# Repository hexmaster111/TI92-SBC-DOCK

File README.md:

**NOTE**
The Zero version is not currently being worked on and is an unusable state

# TI92 - CM4

TODO
--------
- [ ] Whats gonna happon is im gonna get a 4 inch hdmi display and desolder the hdmi connector and add it to a ribbion cable and then add a connector to the pcb for hdmi to interface with that
- [ ] Add a SD card slot
- [x] Figure out what display to use
- [ ] Add a headphone port
- [x] Add a USB Hub
	- [ ] Route USB in a good way :wink:
- [x] Get a charge solution sorted
- [x] Figure out how the keyboard will work and talk to the pi
- [ ] TEST
- [ ] Write code for the ATTINY85 (aka power control chip)
	- [ ] ~~Find a better way to switch power?~~
 - [ ] Use the micro USB that is used for charging to also act as USB OTG for flashing the CM4
 - [ ] Figure out a low voltage cut off for the batCell+ line
 - [ ] Calculate R4 on the charge chip
 - [ ] Make sure all the components will fit in the case with there given footprints
	 - [ ] Measure for LEDS
		 - [ ] Drill Holes for indicators
		 - [ ] Make a nice overlay for indicators 
	 - [ ] Measure for USB Connections
		 - [ ] Modify case

Display
----------
The display being used is a 4 inch SPI display by waveshare and is connected with a pin header, I still have to get the part and check for fitmint for sure, but [this](https://www.waveshare.com/4inch-RPi-LCD-C.htm) looks prmissing

for the display, install accoring to waveshare https://www.waveshare.com/wiki/4inch_HDMI_LCD and deleate all the vc4 overlays and it works (somehow)

Battery Charging
----------
For charging two 18650s I'm using the BQ25887RGET Chip by TI. This chip should have enough current to keep the batteries charged in use. For power input I'm using a Micro USB 

USB Hub
-----------
For a USB hub I'm using the TUSB4041l by Texas instruments, this chip supports 4 downstream ports and 1 upstream, the upstream port is wired directly into the CM4's USB data lines. There are two ports that are connected to standard USB connectors. 

There is also one USB port left unused on the board for internal modifications later on. 

To Get this chip to work, I had to add a 3.3v power supply capable of suppling more current then the pi could, and added the +3.3 High Current Global net. 

To Get this chip to work, I had to add a 1v power supply capable of suppling more current then the pi could, and added the +1 Global net.

Making the keyboard work
----------------------------------
For a keyboard controller I chose to use a 5K5126 which is a programable keyboard controller that supports arbitrary key mapping along with macros and this is all done with a graphical program and uploaded to the keyboard. 
After uploading the matrix and stuff to the controller the idea is to then solder JP2 & JP3. This will then allow the keyboard to communicate with the hub controller and then into the CM4 modal
**note:**  The keyboard controller has some GPIO we can use for a backlight or indicator LEDs, I need to check this out more. 

Power Control
--------
The +5v will go high after the ON button on the keyboard is pressed, this is done using an ATTINY85 and a latching relay, this is done so that I can use this for other single board computers in the future.  
Here is some pseudo code to help understand the idea
```
Use a pin on the pi as a way to know if the system is on and if that pin goes low we disconnect the battery from the 5v converter

if power=off & PowerButton=on //Turn on +5v rail (ColdBoot)
	SETPIN goes high
	wait(50ms)
	SETPIN goes low
	wait(1min)

if PiOnPin=low & power=on  //Shutdown pi after power on pin goes low
	RESETPIN high
	Wait(50ms)
	RESETPIN low

if PiOnPin=high & power=on & PowerButton=on //Force Shutdown 
	if PowerButton = held for 10 sec
		RESETPIN high
		Wait(50ms)
		RESETPIN low	
```

Things to Add Perhaps
---------------------------
- A pointing device
	- A track ball or other pointing device like [this](https://shop.pimoroni.com/products/trackball-breakout). 
	- Perhaps a trackpad
	- Use the Lock/Pinch key as a the key for mouse keys and use the D-Pad as the key mouse
- Some way to have a nice GPIO pin header behind a door for a clean look
- A new keyboard overlay for 2nd keys and the green diamond keys
- Custom keycaps?! (Clear injections would be cool for backlighting)
- Perhaps a ti-92 plus emulator for it (just for fun)

Credits
------
I got the PCB and keyboard layout and matrix diagram from [here](https://github.com/ccadic/TI92-revive). 
Everything else was from the Digi key parts repo or I made.

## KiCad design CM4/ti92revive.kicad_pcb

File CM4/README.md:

# TI92 RPI Zero
 Putting a zero in a 92 + calc

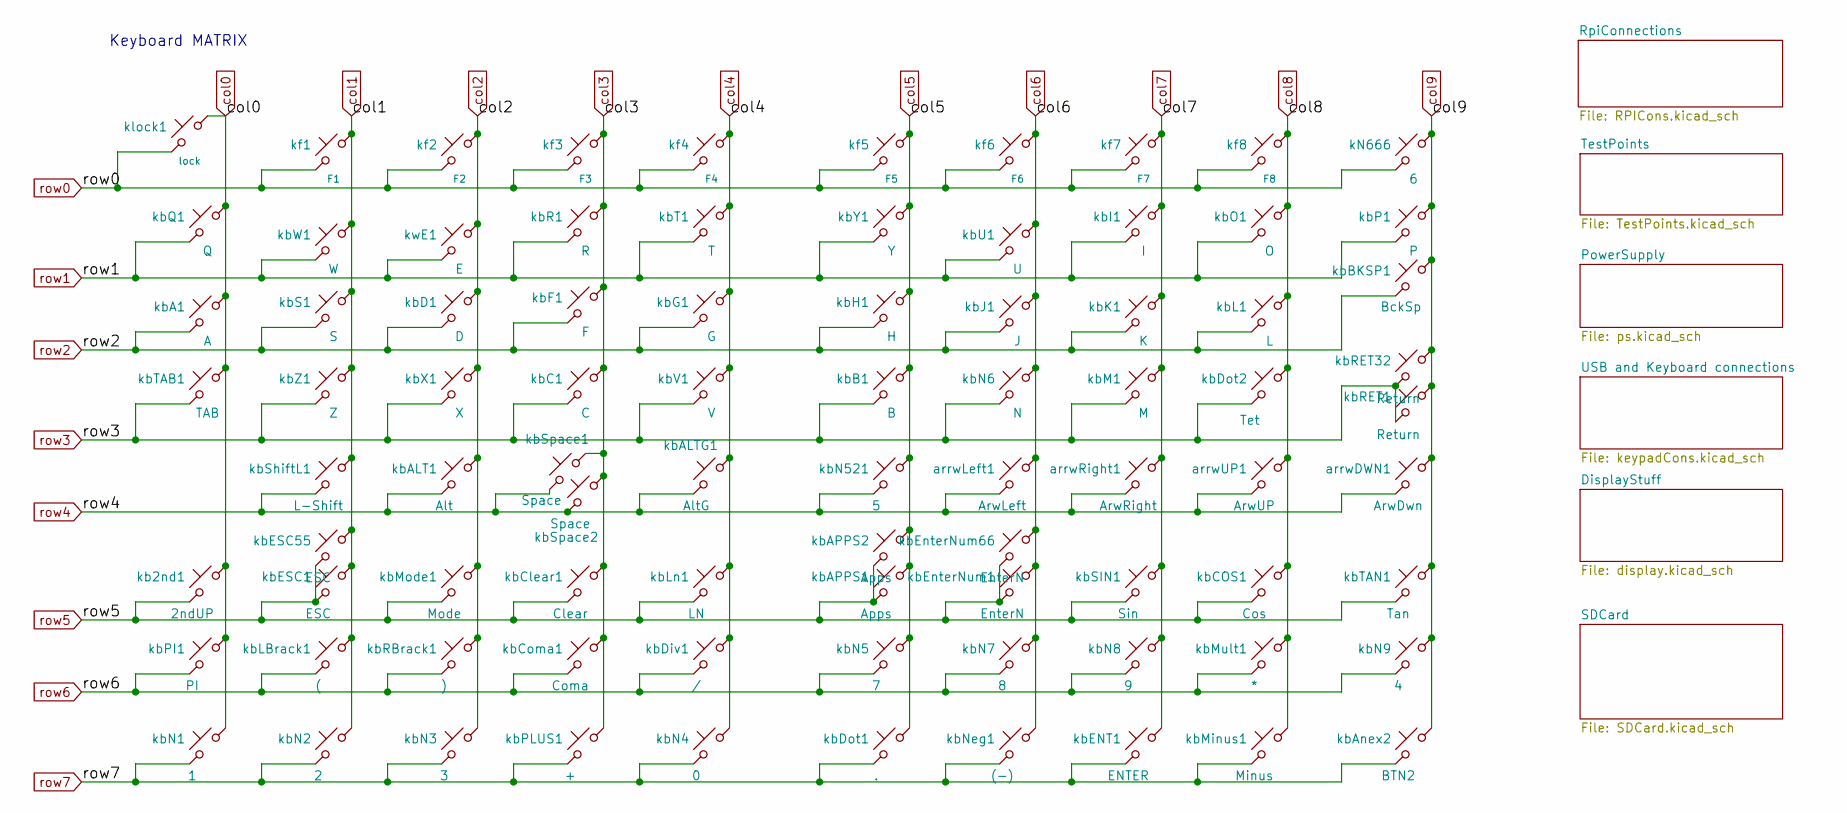
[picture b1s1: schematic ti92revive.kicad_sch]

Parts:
arrwDWN1: ArwDwn; Kbpad
arrwLeft1: ArwLeft; Kbpad
arrwRight1: ArwRight; Kbpad
arrwUP1: ArwUP; Kbpad
kN666: 6; Kbpad
kb2nd1: 2ndUP; Kbpad
kbA1: A; Kbpad
kbALT1: Alt; Kbpad
kbALTG1: AltG; Kbpad
kbAPPS1, kbAPPS2: Apps; Kbpad
kbAnex2: BTN2; Kbpad
kbB1: B; Kbpad
kbBKSP1: BckSp; Kbpad
kbC1: C; Kbpad
kbCOS1: Cos; Kbpad
kbClear1: Clear; Kbpad
kbComa1: Coma; Kbpad
kbD1: D; Kbpad
kbDiv1: /; Kbpad
kbDot1: .; Kbpad
kbDot2: Tet; Kbpad
kbENT1: ENTER; Kbpad
kbESC1, kbESC55: ESC; Kbpad
kbEnterNum1, kbEnterNum66: EnterN; Kbpad
kbF1: F; Kbpad
kbG1: G; Kbpad
kbH1: H; Kbpad
kbI1: I; Kbpad
kbJ1: J; Kbpad
kbK1: K; Kbpad
kbL1: L; Kbpad
kbLBrack1: (; Kbpad
kbLn1: LN; Kbpad
kbM1: M; Kbpad
kbMinus1: Minus; Kbpad
kbMode1: Mode; Kbpad
kbMult1: *; Kbpad
kbN1: 1; Kbpad
kbN2: 2; Kbpad
kbN3: 3; Kbpad
kbN4: 0; Kbpad
kbN5: 7; Kbpad
kbN6: N; Kbpad
kbN7: 8; Kbpad
kbN8: 9; Kbpad
kbN9: 4; Kbpad
kbN521: 5; Kbpad
kbNeg1: (-); Kbpad
kbO1: O; Kbpad
kbP1: P; Kbpad
kbPI1: PI; Kbpad
kbPLUS1: +; Kbpad
kbQ1: Q; Kbpad
kbR1: R; Kbpad
kbRBrack1: ); Kbpad
kbRET1, kbRET32: Return; Kbpad
kbS1: S; Kbpad
kbSIN1: Sin; Kbpad
kbShiftL1: L-Shift; Kbpad
kbSpace1, kbSpace2: Space; Kbpad
kbT1: T; Kbpad
kbTAB1: TAB; Kbpad
kbTAN1: Tan; Kbpad
kbU1: U; Kbpad
kbV1: V; Kbpad
kbW1: W; Kbpad
kbX1: X; Kbpad
kbY1: Y; Kbpad
kbZ1: Z; Kbpad
kf1: F1; Kbpad
kf2: F2; Kbpad
kf3: F3; Kbpad
kf4: F4; Kbpad
kf5: F5; Kbpad
kf6: F6; Kbpad
kf7: F7; Kbpad
kf8: F8; Kbpad
klock1: lock; Kbpad
kwE1: E; Kbpad

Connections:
col0: kb2nd1.1, kbA1.1, kbN1.1, kbPI1.1, kbQ1.1, kbTAB1.1, klock1.1; also elsewhere on the board
col1: kbESC1.1, kbESC55.1, kbLBrack1.1, kbN2.1, kbS1.1, kbShiftL1.1, kbW1.1, kbZ1.1, kf1.1; also elsewhere on the board
col2: kbALT1.1, kbD1.1, kbMode1.1, kbN3.1, kbRBrack1.1, kbX1.1, kf2.1, kwE1.1; also elsewhere on the board
col3: kbC1.1, kbClear1.1, kbComa1.1, kbF1.1, kbPLUS1.1, kbR1.1, kbSpace1.1, kbSpace2.1, kf3.1; also elsewhere on the board
col4: kbALTG1.1, kbDiv1.1, kbG1.1, kbLn1.1, kbN4.1, kbT1.1, kbV1.1, kf4.1; also elsewhere on the board
col5: kbAPPS1.1, kbAPPS2.1, kbB1.1, kbDot1.1, kbH1.1, kbN5.1, kbN521.1, kbY1.1, kf5.1; also elsewhere on the board
col6: arrwLeft1.1, kbEnterNum1.1, kbEnterNum66.1, kbJ1.1, kbN6.1, kbN7.1, kbNeg1.1, kbU1.1, kf6.1; also elsewhere on the board
col7: arrwRight1.1, kbENT1.1, kbI1.1, kbK1.1, kbM1.1, kbN8.1, kbSIN1.1, kf7.1; also elsewhere on the board
col8: arrwUP1.1, kbCOS1.1, kbDot2.1, kbL1.1, kbMinus1.1, kbMult1.1, kbO1.1, kf8.1; also elsewhere on the board
col9: arrwDWN1.1, kN666.1, kbAnex2.1, kbBKSP1.1, kbN9.1, kbP1.1, kbRET1.1, kbRET32.1, kbTAN1.1; also elsewhere on the board
row0: kN666.2, kf1.2, kf2.2, kf3.2, kf4.2, kf5.2, kf6.2, kf7.2, kf8.2, klock1.2; also elsewhere on the board
row1: kbI1.2, kbO1.2, kbP1.2, kbQ1.2, kbR1.2, kbT1.2, kbU1.2, kbW1.2, kbY1.2, kwE1.2; also elsewhere on the board
row2: kbA1.2, kbBKSP1.2, kbD1.2, kbF1.2, kbG1.2, kbH1.2, kbJ1.2, kbK1.2, kbL1.2, kbS1.2; also elsewhere on the board
row3: kbB1.2, kbC1.2, kbDot2.2, kbM1.2, kbN6.2, kbRET1.2, kbRET32.2, kbTAB1.2, kbV1.2, kbX1.2, kbZ1.2; also elsewhere on the board
row4: arrwDWN1.2, arrwLeft1.2, arrwRight1.2, arrwUP1.2, kbALT1.2, kbALTG1.2, kbN521.2, kbShiftL1.2, kbSpace1.2, kbSpace2.2; also elsewhere on the board
row5: kb2nd1.2, kbAPPS1.2, kbAPPS2.2, kbCOS1.2, kbClear1.2, kbESC1.2, kbESC55.2, kbEnterNum1.2, kbEnterNum66.2, kbLn1.2, kbMode1.2, kbSIN1.2, kbTAN1.2; also elsewhere on the board
row6: kbComa1.2, kbDiv1.2, kbLBrack1.2, kbMult1.2, kbN5.2, kbN7.2, kbN8.2, kbN9.2, kbPI1.2, kbRBrack1.2; also elsewhere on the board
row7: kbAnex2.2, kbDot1.2, kbENT1.2, kbMinus1.2, kbN1.2, kbN2.2, kbN3.2, kbN4.2, kbNeg1.2, kbPLUS1.2; also elsewhere on the board

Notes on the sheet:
Keyboard MATRIX

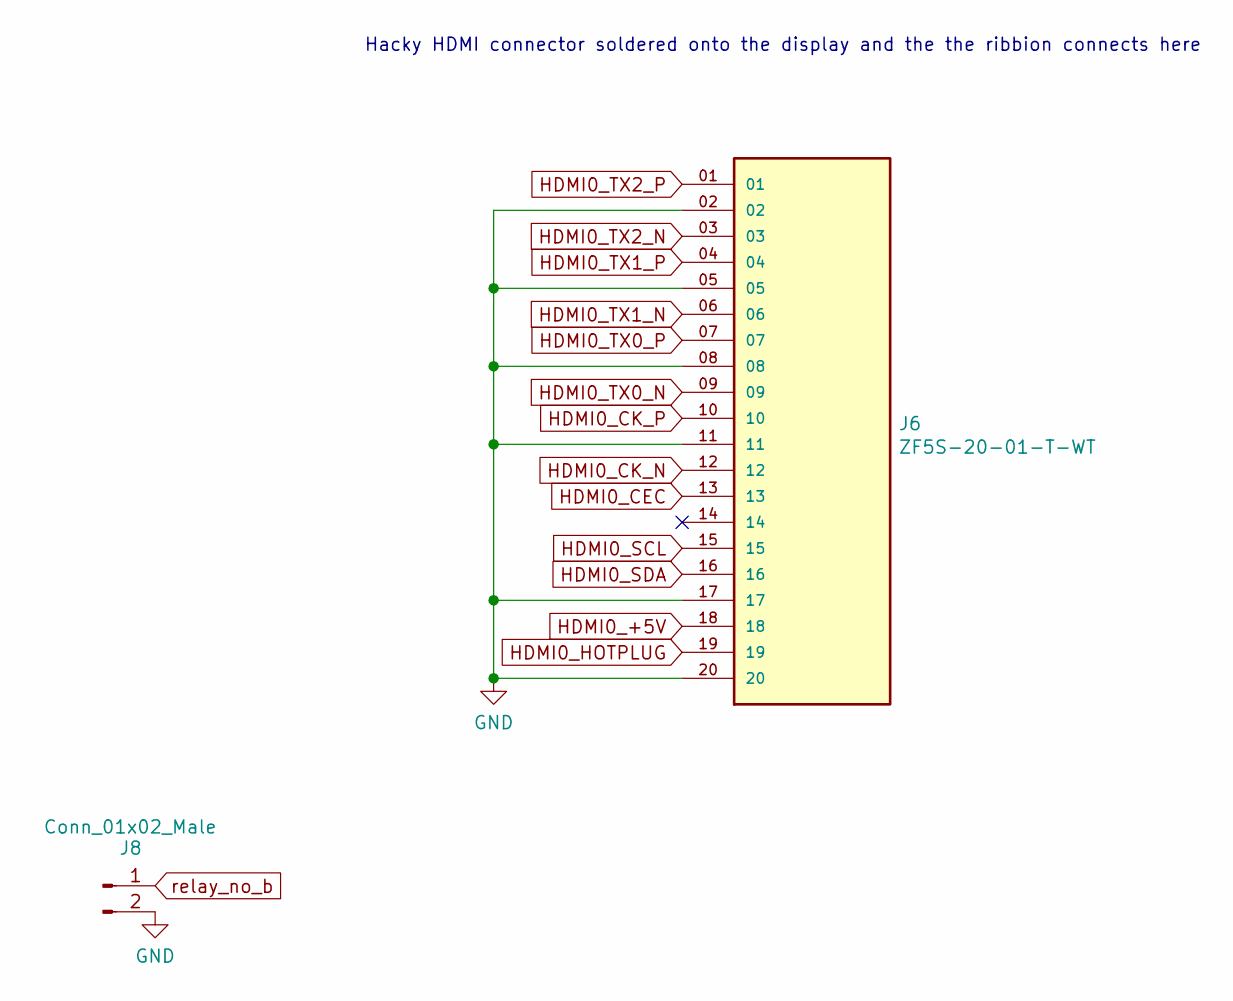
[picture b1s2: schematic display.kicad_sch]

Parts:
J6: ZF5S-20-01-T-WT; SAMTEC_ZF5S-20-01-T-WT
J8: Conn_01x02_Male; PinHeader_1x02_P1.00mm_Vertical

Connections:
Earth_Clean: J6.02, J6.05, J6.08, J6.11, J6.17, J6.20, J8.2; also elsewhere on the board
HDMI0_+5V: J6.18
HDMI0_CEC: J6.13; also elsewhere on the board
HDMI0_CK_N: J6.12; also elsewhere on the board
HDMI0_CK_P: J6.10; also elsewhere on the board
HDMI0_HOTPLUG: J6.19; also elsewhere on the board
HDMI0_SCL: J6.15; also elsewhere on the board
HDMI0_SDA: J6.16; also elsewhere on the board
HDMI0_TX0_N: J6.09; also elsewhere on the board
HDMI0_TX0_P: J6.07; also elsewhere on the board
HDMI0_TX1_N: J6.06; also elsewhere on the board
HDMI0_TX1_P: J6.04; also elsewhere on the board
HDMI0_TX2_N: J6.03; also elsewhere on the board
HDMI0_TX2_P: J6.01; also elsewhere on the board
relay_no_b: J8.1; also elsewhere on the board

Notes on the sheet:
Hacky HDMI connector soldered onto the display and the the ribbion connects here

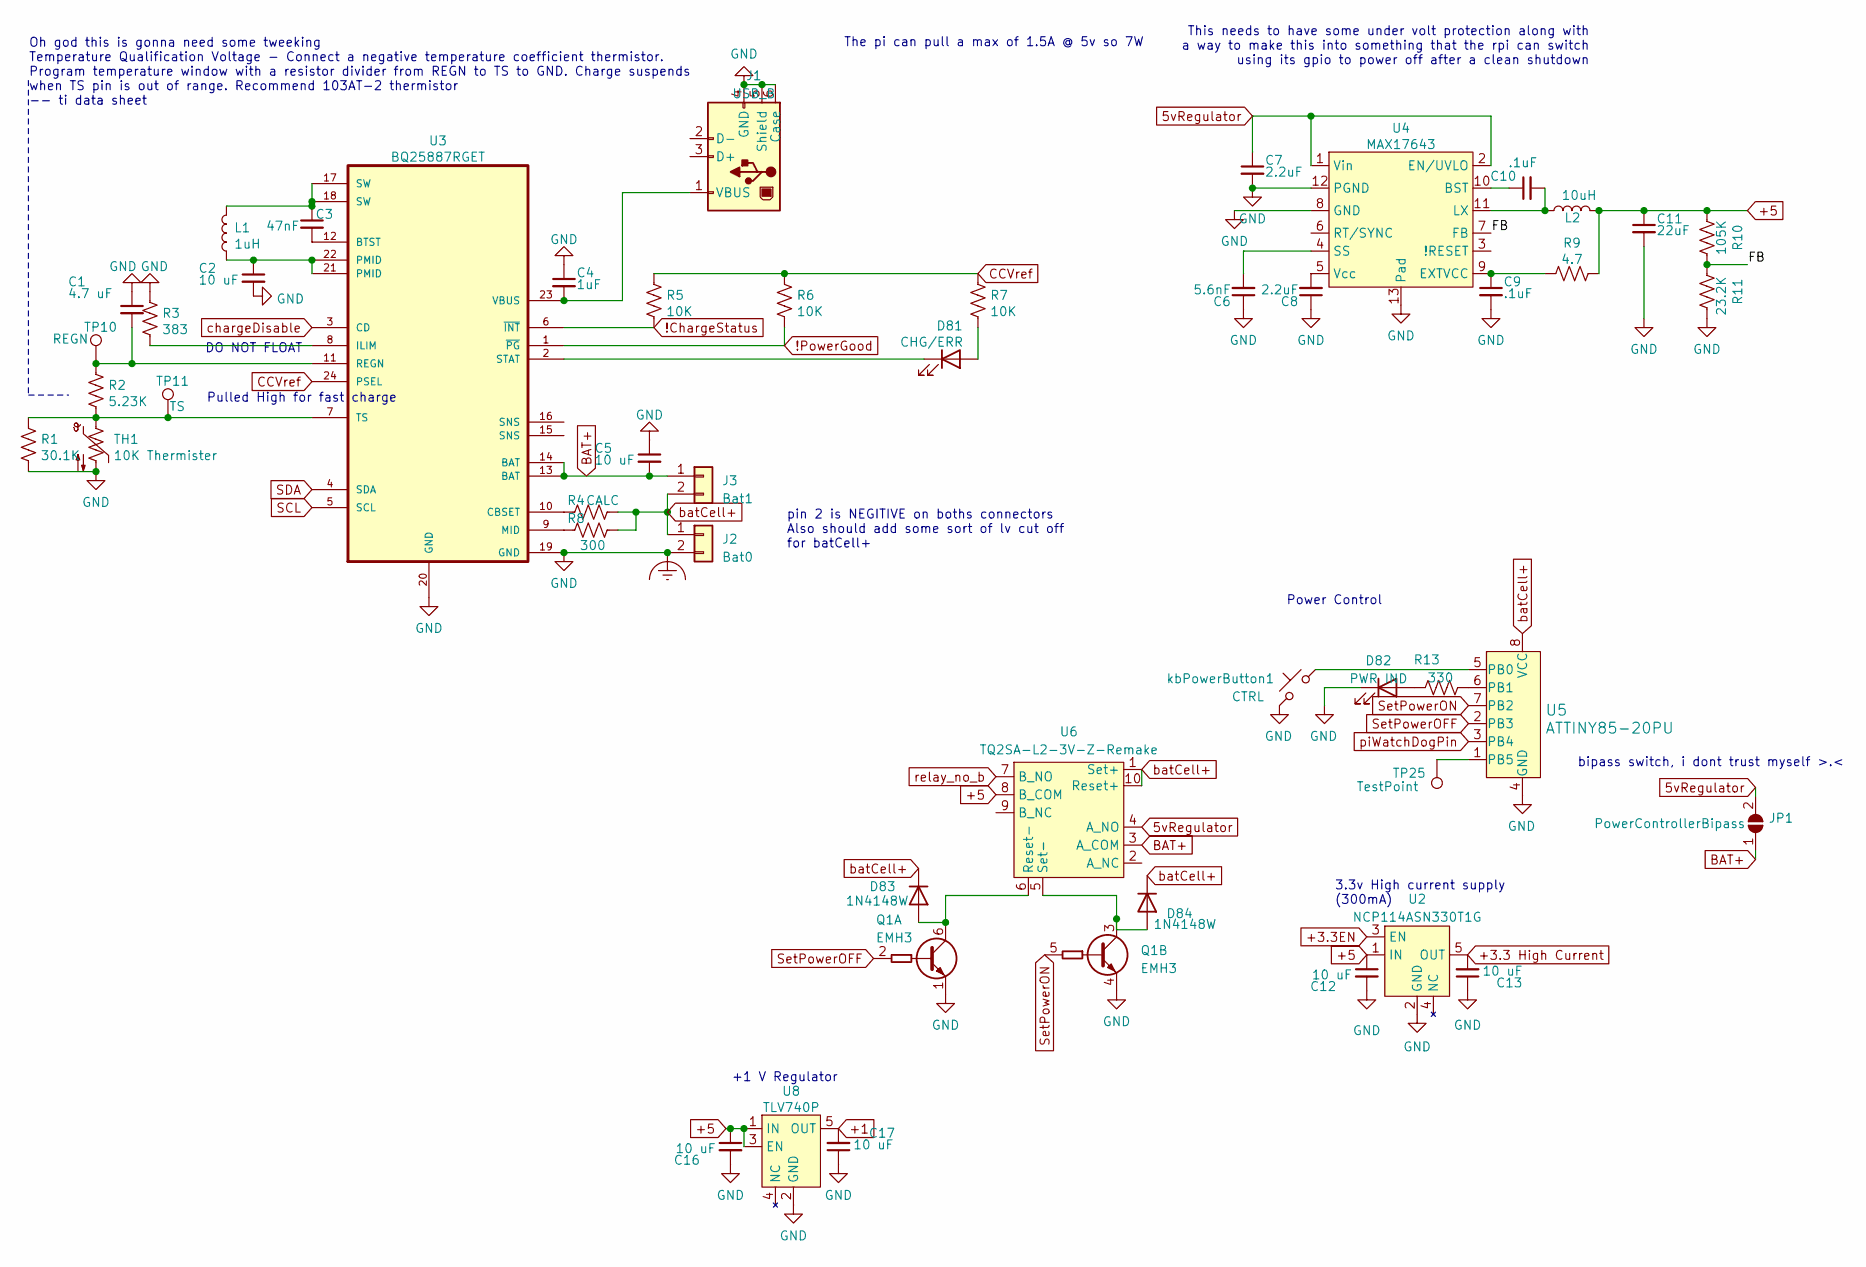
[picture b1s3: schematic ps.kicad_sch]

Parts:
C1: 4.7 uF; C_1206_3216Metric
C2, C5, C12, C13, C16, C17: 10 uF; C_1206_3216Metric
C3: 47nF; C_1206_3216Metric
C4: 1uF; C_1206_3216Metric
C6: 5.6nF; C_1206_3216Metric
C7, C8: 2.2uF; C_1206_3216Metric
C9, C10: .1uF; C_1206_3216Metric
C11: 22uF; C_1206_3216Metric
D81: CHG/ERR; LED_1206_3216Metric_Pad1.42x1.75mm_HandSolder
D82: PWR IND; LED_1206_3216Metric_Pad1.42x1.75mm_HandSolder
D83, D84: 1N4148W; D_SOD-123
J1: USB_B; USB_Micro-B_Amphenol_10103594-0001LF_Horizontal
J2: Bat0; PinHeader_1x02_P2.54mm_Horizontal
J3: Bat1; PinHeader_1x02_P2.54mm_Horizontal
JP1: PowerControllerBipass; SolderJumper-2_P1.3mm_Open_RoundedPad1.0x1.5mm
L1: 1uH; L_1812_4532Metric
L2: 10uH; L_1812_4532Metric
Q1: EMH3; SOT-563
R1: 30.1K; R_1206_3216Metric
R2: 5.23K; R_1206_3216Metric
R3: 383; R_1206_3216Metric
R4: CALC; R_1206_3216Metric
R5, R6, R7: 10K; R_1206_3216Metric
R8: 300; R_1206_3216Metric
R9: 4.7; R_1206_3216Metric
R10: 105K; R_1206_3216Metric
R11: 23.2K; R_1206_3216Metric
R13: 330; R_1206_3216Metric
TH1: 10K Thermister; PinHeader_1x02_P2.54mm_Horizontal
TP10: REGN; TestPoint_Pad_1.0x1.0mm
TP11: TS; TestPoint_Pad_1.0x1.0mm
TP25: TestPoint; TestPoint_Pad_D1.0mm
U2: NCP114ASN330T1G; TSOT-23-5_HandSoldering
U3: BQ25887RGET; VQFN-24-1EP_4x4mm_P0.5mm_EP2.45x2.45mm_ThermalVias
U4: MAX17643; TDFN-12_3x3mm_P0.5mm
U5: ATTINY85-20PU; DIP-8_W7.62mm; MPN ATTINY85-20PU; Digi-Key_PN ATTINY85-20PU-ND
U6: TQ2SA-L2-3V-Z-Remake; TQ2SA-L2-3V-Z
U8: TLV740P; SOT-23-5_HandSoldering
kbPowerButton1: CTRL; Kbpad

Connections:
5vRegulator: C7.1, JP1.2 (B), U4.1 (Vin), U4.2 (EN/UVLO), U6.4 (A_NO)
!ChargeStatus: R5.1, U3.6 (~INT)
!PowerGood: R6.1, U3.1 (~PG)
+1: C17.2, U8.5 (OUT); also elsewhere on the board
+1.8: U2.3 (EN); also elsewhere on the board
+3.3 High Current: C13.2, U2.5 (OUT); also elsewhere on the board
+5: C11.1, C12.1, C16.1, L2.2, R9.2, R10.1, U2.1 (IN), U6.8 (B_COM), U8.1 (IN), U8.3 (EN); also elsewhere on the board
/PowerSupply/FB: R10.2, R11.1, U4.7 (FB)
BAT+: C5.2, J3.1, JP1.1 (A), U3.13 (BAT), U3.14 (BAT), U6.3 (A_COM)
CCVref: R5.2, R6.2, R7.2, U3.24 (PSEL)
Earth_Clean: C1.1, C2.2, C4.1, C5.1, C6.1, C7.2, C8.1, C9.2, C11.2, C12.2, C13.1, C16.2, C17.1, D82.1 (K), J1.4 (GND), J1.5 (Shield), J1.6 (Case), J2.2, Q1.1 (E1), Q1.4 (E2), R1.1, R3.1, R11.2, TH1.2, U2.2 (GND), U3.19 (GND), U3.20 (GND), U4.8 (GND), U4.12 (PGND), U4.13 (Pad), U5.4 (GND), U8.2 (GND), kbPowerButton1.2; also elsewhere on the board
unnamed: C1.2, R2.2, TP10.1, U3.11 (REGN)
unnamed: C2.1, L1.1, U3.21 (PMID), U3.22 (PMID)
unnamed: C3.1, L1.2, U3.17 (SW), U3.18 (SW)
unnamed: C3.2, U3.12 (BTST)
unnamed: C4.2, J1.1 (VBUS), U3.23 (VBUS)
unnamed: C6.2, U4.4 (SS)
unnamed: C8.2, U4.5 (Vcc)
unnamed: C9.1, R9.1, U4.9 (EXTVCC)
unnamed: C10.1, U4.10 (BST)
unnamed: C10.2, L2.1, U4.11 (LX)
unnamed: D81.1 (K), U3.2 (STAT)
unnamed: D81.2 (A), R7.1
unnamed: D82.2 (A), R13.2
unnamed: D83.2 (A), Q1.6 (C1), U6.6 (Reset-)
unnamed: D84.2 (A), Q1.3 (C2), U6.5 (Set-)
unnamed: R1.2, R2.1, TH1.1, TP11.1, U3.7 (TS)
unnamed: R3.2, U3.8 (ILIM)
unnamed: R4.2, U3.10 (CBSET)
unnamed: R8.2, U3.9 (MID)
unnamed: R13.1, U5.6 (PB1)
unnamed: TP25.1, U5.1 (PB5)
unnamed: U5.5 (PB0), kbPowerButton1.1
SCL: U3.5 (SCL); also elsewhere on the board
SDA: U3.4 (SDA); also elsewhere on the board
SetPowerOFF: Q1.2 (B1), U5.2 (PB3)
SetPowerON: Q1.5 (B2), U5.7 (PB2)
batCell+: D83.1 (K), D84.1 (K), J2.1, J3.2, R4.1, R8.1, U5.8 (VCC), U6.1 (Set+), U6.10 (Reset+)
chargeDisable: U3.3 (CD)
piWatchDogPin: U5.3 (PB4); also elsewhere on the board
relay_no_b: U6.7 (B_NO); also elsewhere on the board

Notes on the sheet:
Oh god this is gonna need some tweeking Temperature Qualification Voltage - Connect a negative temperature coefficient thermistor. Program temperature window with a resistor divider from REGN to TS to GND. Charge suspends when TS pin is out of range. Recommend 103AT-2 thermistor -- ti data sheet
DO NOT FLOAT
Pulled High for fast charge
pin 2 is NEGITIVE on boths connectors Also should add some sort of lv cut off for batCell+
+1 V Regulator
The pi can pull a max of 1.5A @ 5v so 7W
3.3v High current supply (300mA)
Power Control
This needs to have some under volt protection along with a way to make this into something that the rpi can switch using its gpio to power off after a clean shutdown
bipass switch, i dont trust myself >.<

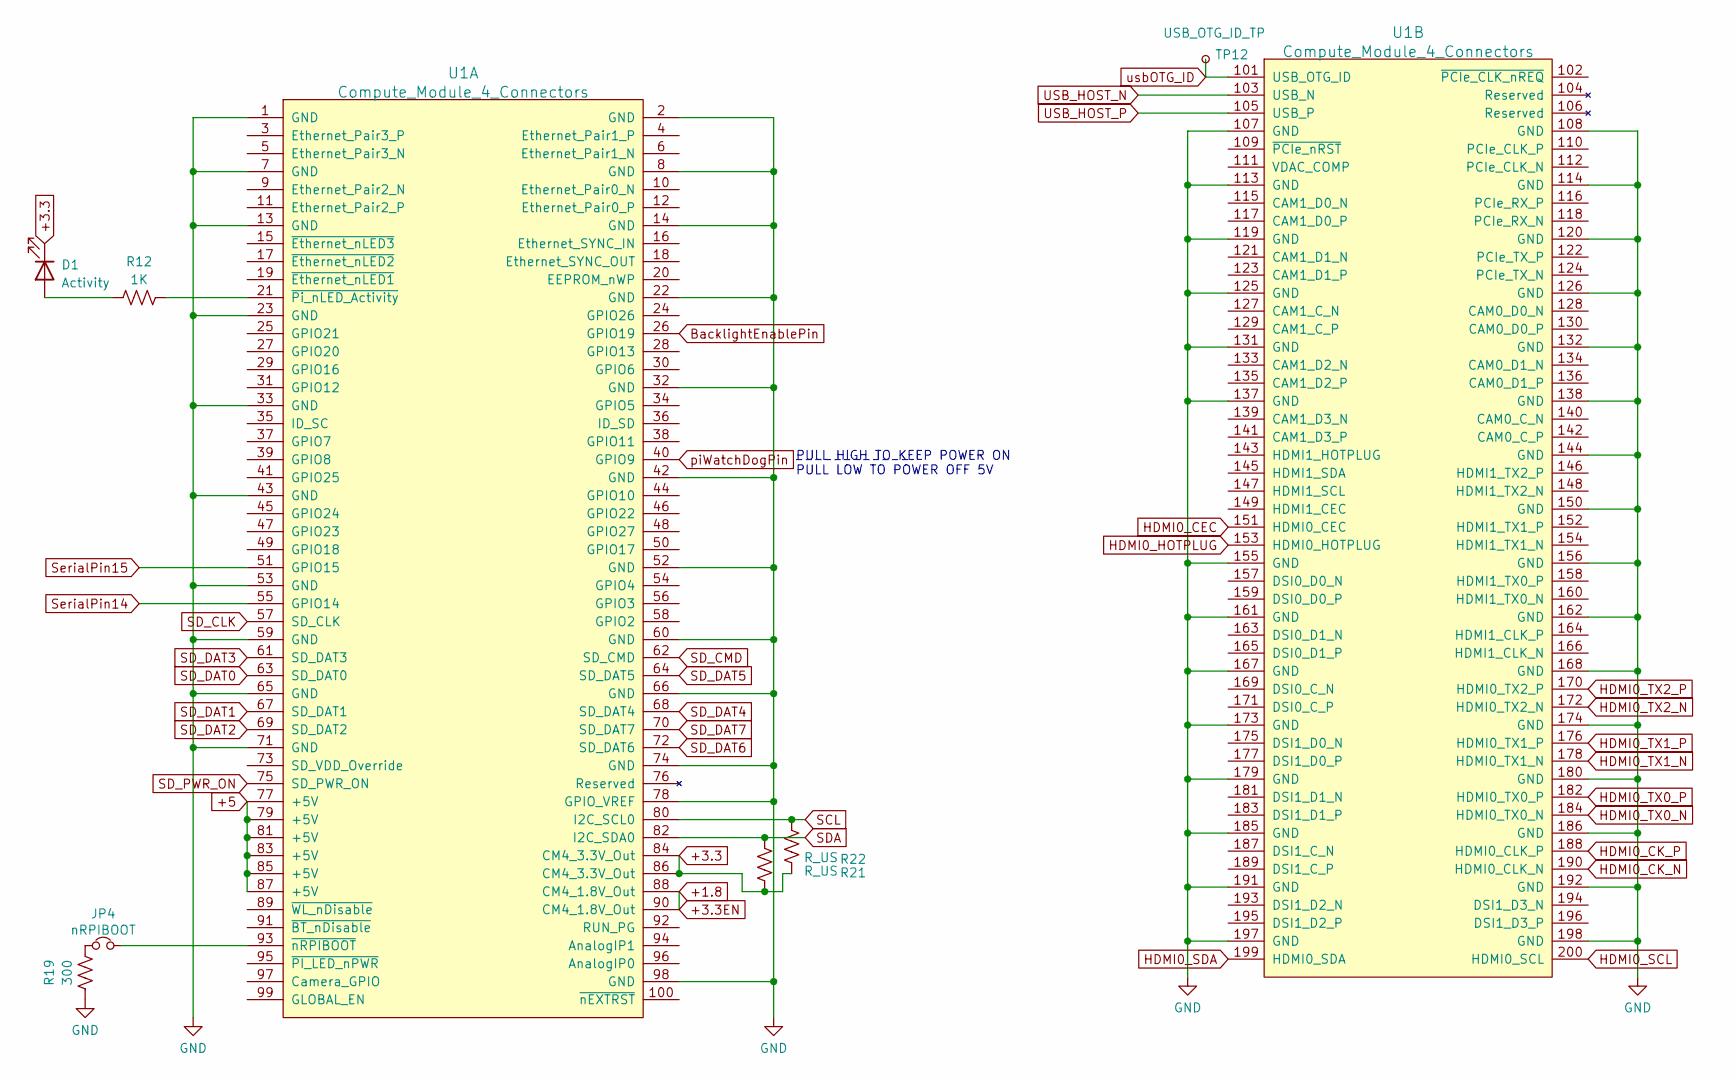
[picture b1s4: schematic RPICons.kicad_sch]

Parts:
D1: Activity; LED_1206_3216Metric_Pad1.42x1.75mm_HandSolder
JP4: nRPIBOOT; PinHeader_1x02_P2.54mm_Horizontal
R12: 1K; R_1206_3216Metric
R19: 300; R_1206_3216Metric
R21, R22: R_US; R_1206_3216Metric
TP12: USB_OTG_ID_TP; TestPoint_Pad_D1.0mm
U1: Compute_Module_4_Connectors; Raspberry-Pi-4-Compute-Module

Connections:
+1.8: U1.88 (CM4_1.8V_Out), U1.90 (CM4_1.8V_Out); also elsewhere on the board
+3.3: D1.1 (K), R21.2, R22.2, U1.84 (CM4_3.3V_Out), U1.86 (CM4_3.3V_Out); also elsewhere on the board
+5: U1.77 (+5V), U1.79 (+5V), U1.81 (+5V), U1.83 (+5V), U1.85 (+5V), U1.87 (+5V); also elsewhere on the board
BacklightEnablePin: U1.26 (GPIO19)
Earth_Clean: R19.1, U1.1 (GND), U1.2 (GND), U1.7 (GND), U1.8 (GND), U1.13 (GND), U1.14 (GND), U1.22 (GND), U1.23 (GND), U1.32 (GND), U1.33 (GND), U1.42 (GND), U1.43 (GND), U1.52 (GND), U1.53 (GND), U1.59 (GND), U1.60 (GND), U1.65 (GND), U1.66 (GND), U1.71 (GND), U1.74 (GND), U1.78 (GPIO_VREF), U1.98 (GND), U1.107 (GND), U1.108 (GND), U1.113 (GND), U1.114 (GND), U1.119 (GND), U1.120 (GND), U1.125 (GND), U1.126 (GND), U1.131 (GND), U1.132 (GND), U1.137 (GND), U1.138 (GND), U1.144 (GND), U1.150 (GND), U1.155 (GND), U1.156 (GND), U1.161 (GND), U1.162 (GND), U1.167 (GND), U1.168 (GND), U1.173 (GND), U1.174 (GND), U1.179 (GND), U1.180 (GND), U1.185 (GND), U1.186 (GND), U1.191 (GND), U1.192 (GND), U1.197 (GND), U1.198 (GND); also elsewhere on the board
HDMI0_CEC: U1.151 (HDMI0_CEC); also elsewhere on the board
HDMI0_CK_N: U1.190 (HDMI0_CLK_N); also elsewhere on the board
HDMI0_CK_P: U1.188 (HDMI0_CLK_P); also elsewhere on the board
HDMI0_HOTPLUG: U1.153 (HDMI0_HOTPLUG); also elsewhere on the board
HDMI0_SCL: U1.200 (HDMI0_SCL); also elsewhere on the board
HDMI0_SDA: U1.199 (HDMI0_SDA); also elsewhere on the board
HDMI0_TX0_N: U1.184 (HDMI0_TX0_N); also elsewhere on the board
HDMI0_TX0_P: U1.182 (HDMI0_TX0_P); also elsewhere on the board
HDMI0_TX1_N: U1.178 (HDMI0_TX1_N); also elsewhere on the board
HDMI0_TX1_P: U1.176 (HDMI0_TX1_P); also elsewhere on the board
HDMI0_TX2_N: U1.172 (HDMI0_TX2_N); also elsewhere on the board
HDMI0_TX2_P: U1.170 (HDMI0_TX2_P); also elsewhere on the board
unnamed: D1.2 (A), R12.1
unnamed: JP4.1, R19.2
unnamed: JP4.2, U1.93 (~nRPIBOOT)
unnamed: R12.2, U1.21 (~Pi_nLED_Activity)
SCL: R22.1, U1.80 (I2C_SCL0); also elsewhere on the board
SDA: R21.1, U1.82 (I2C_SDA0); also elsewhere on the board
SD_CLK: U1.57 (SD_CLK); also elsewhere on the board
SD_CMD: U1.62 (SD_CMD); also elsewhere on the board
SD_DAT0: U1.63 (SD_DAT0); also elsewhere on the board
SD_DAT1: U1.67 (SD_DAT1); also elsewhere on the board
SD_DAT2: U1.69 (SD_DAT2); also elsewhere on the board
SD_DAT3: U1.61 (SD_DAT3); also elsewhere on the board
SD_DAT4: U1.68 (SD_DAT4)
SD_DAT5: U1.64 (SD_DAT5)
SD_DAT6: U1.72 (SD_DAT6)
SD_DAT7: U1.70 (SD_DAT7)
SD_PWR_ON: U1.75 (SD_PWR_ON)
SerialPin14: U1.55 (GPIO14); also elsewhere on the board
SerialPin15: U1.51 (GPIO15); also elsewhere on the board
USB_HOST_N: U1.103 (USB_N); also elsewhere on the board
USB_HOST_P: U1.105 (USB_P); also elsewhere on the board
piWatchDogPin: U1.40 (GPIO9); also elsewhere on the board
usbOTG_ID: TP12.1, U1.101 (USB_OTG_ID)

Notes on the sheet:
PULL HIGH TO KEEP POWER ON PULL LOW TO POWER OFF 5V

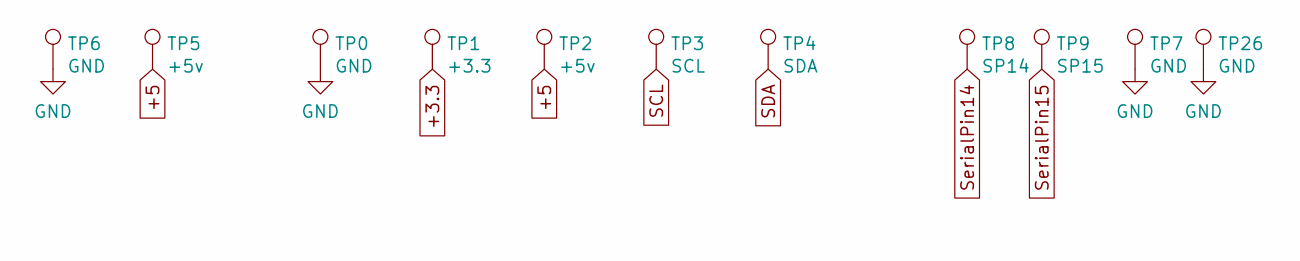
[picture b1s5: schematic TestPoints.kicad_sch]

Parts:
TP0, TP6, TP7, TP26: GND; TestPoint_Pad_D1.5mm
TP1: +3.3; TestPoint_Pad_D1.5mm
TP2, TP5: +5v; TestPoint_Pad_D1.5mm
TP3: SCL; TestPoint_Pad_D1.5mm
TP4: SDA; TestPoint_Pad_D1.5mm
TP8: SP14; TestPoint_Pad_D1.5mm
TP9: SP15; TestPoint_Pad_D1.5mm

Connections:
+3.3: TP1.1; also elsewhere on the board
+5: TP2.1, TP5.1; also elsewhere on the board
Earth_Clean: TP0.1, TP6.1, TP7.1, TP26.1; also elsewhere on the board
SCL: TP3.1; also elsewhere on the board
SDA: TP4.1; also elsewhere on the board
SerialPin14: TP8.1; also elsewhere on the board
SerialPin15: TP9.1; also elsewhere on the board

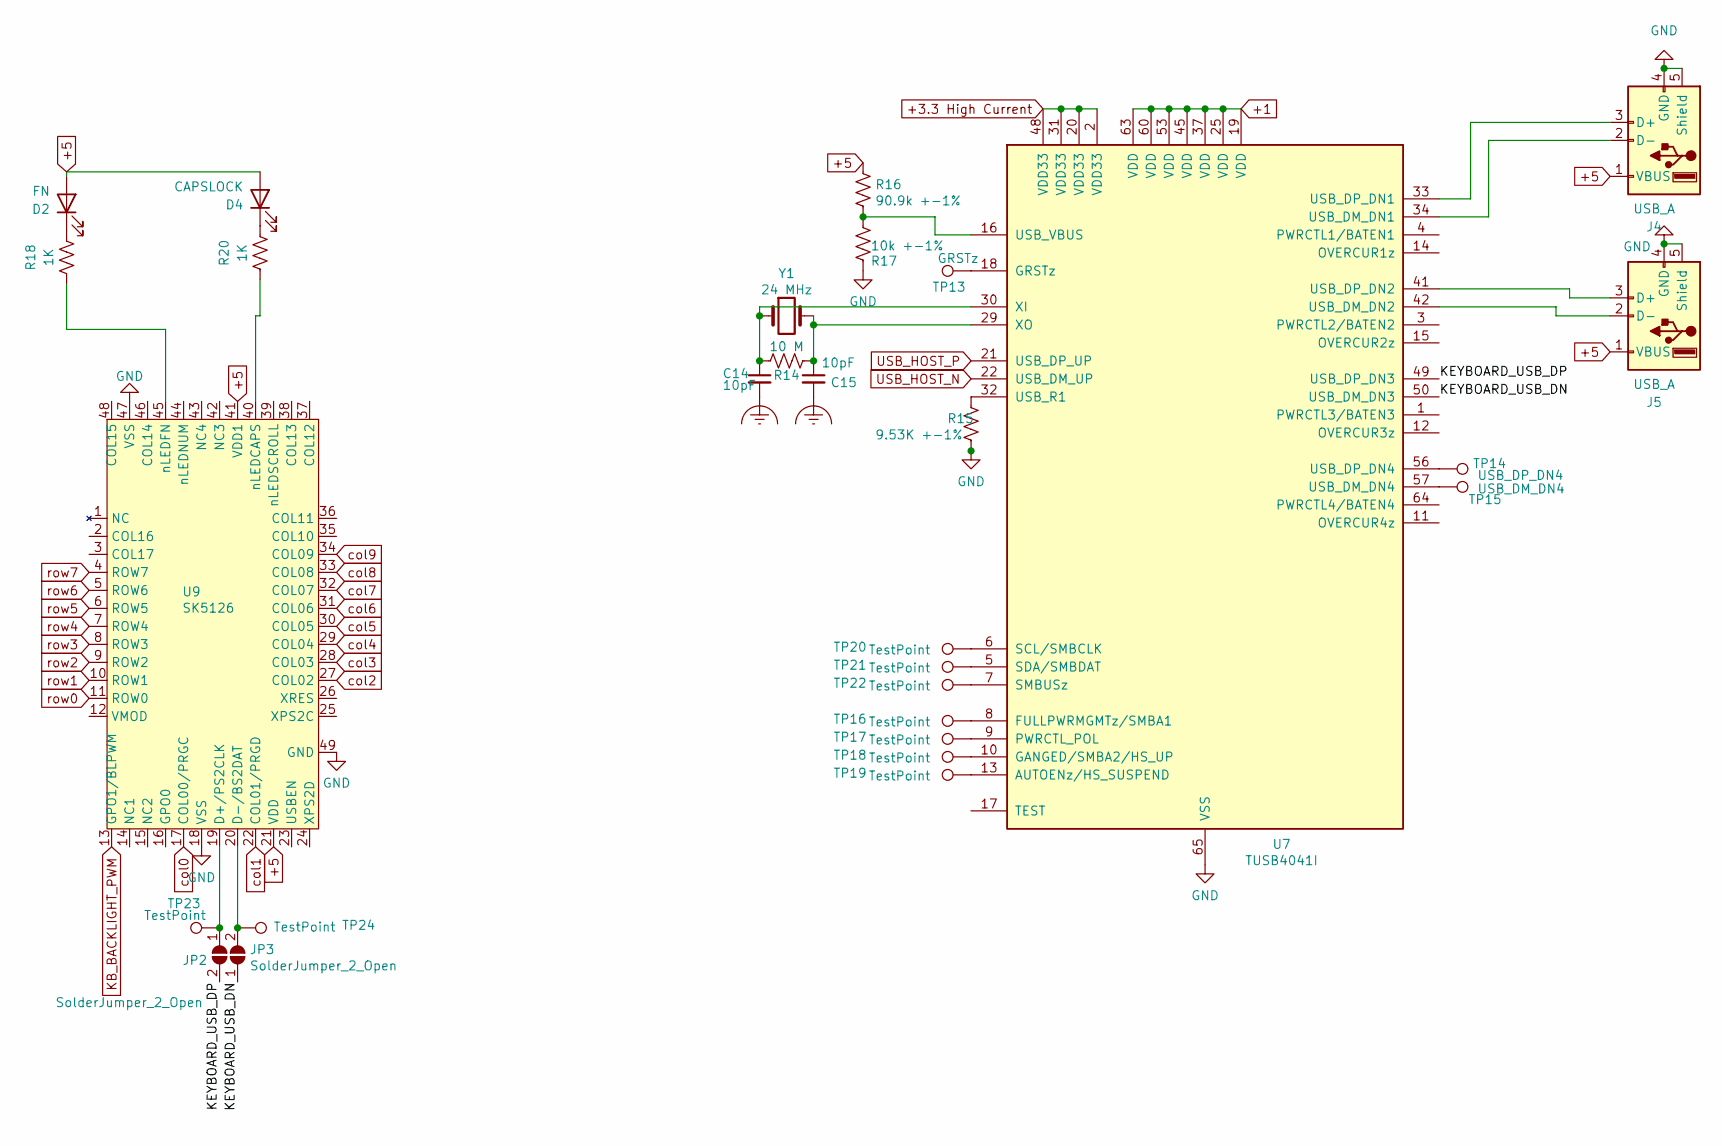
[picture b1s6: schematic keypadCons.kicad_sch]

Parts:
C14, C15: 10pF; C_1206_3216Metric
D2: FN; LED_1206_3216Metric_Pad1.42x1.75mm_HandSolder
D4: CAPSLOCK; LED_1206_3216Metric_Pad1.42x1.75mm_HandSolder
J4, J5: USB_A; USB_A_Stewart_SS-52100-001_Horizontal
JP2, JP3: SolderJumper_2_Open; SolderJumper-2_P1.3mm_Open_RoundedPad1.0x1.5mm
R14: 10 M; R_2010_5025Metric_Pad1.40x2.65mm_HandSolder
R15: 9.53K +-1%; R_2010_5025Metric_Pad1.40x2.65mm_HandSolder
R16: 90.9k +-1%; R_2010_5025Metric_Pad1.40x2.65mm_HandSolder
R17: 10k +-1%; R_2010_5025Metric_Pad1.40x2.65mm_HandSolder
R18, R20: 1K; R_1206_3216Metric
TP13: GRSTz; TestPoint_Pad_1.0x1.0mm
TP14: USB_DP_DN4; TestPoint_Pad_1.0x1.0mm
TP15: USB_DM_DN4; TestPoint_Pad_1.0x1.0mm
TP16, TP17, TP18, TP19, TP20, TP21, TP22, TP23, TP24: TestPoint; TestPoint_Pad_1.0x1.0mm
U7: TUSB4041I; HTQFP-64-1EP_10x10mm_P0.5mm_EP8x8mm_Mask4.4x4.4mm_ThermalVi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
U9: SK5126; QFN-48-1EP_7x7mm_P0.5mm_EP5.6x5.6mm
Y1: 24 MHz; HCM49_E

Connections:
+1: U7.19 (VDD), U7.25 (VDD), U7.37 (VDD), U7.45 (VDD), U7.53 (VDD), U7.60 (VDD), U7.63 (VDD); also elsewhere on the board
+3.3 High Current: U7.2 (VDD33), U7.20 (VDD33), U7.31 (VDD33), U7.48 (VDD33); also elsewhere on the board
+5: D2.2 (A), D4.2 (A), J4.1 (VBUS), J5.1 (VBUS), R16.1, U9.21 (VDD), U9.41 (VDD1); also elsewhere on the board
/USB and Keyboard connections/KEYBOARD_USB_DN: JP3.1 (A), U7.50 (USB_DM_DN3)
/USB and Keyboard connections/KEYBOARD_USB_DP: JP2.2 (B), U7.49 (USB_DP_DN3)
Earth_Clean: C14.2, C15.2, J4.4 (GND), J4.5 (Shield), J5.4 (GND), J5.5 (Shield), R15.2, R17.2, U7.46 (RSVD), U7.65 (VSS), U9.18 (VSS), U9.47 (VSS), U9.49 (GND); also elsewhere on the board
KB_BACKLIGHT_PWM: U9.13 (GPO1/BLPWM)
unnamed: C14.1, R14.2, U7.30 (XI), Y1.1
unnamed: C15.1, R14.1, U7.29 (XO), Y1.2
unnamed: D2.1 (K), R18.2
unnamed: D4.1 (K), R20.2
unnamed: J4.2 (D-), U7.34 (USB_DM_DN1)
unnamed: J4.3 (D+), U7.33 (USB_DP_DN1)
unnamed: J5.2 (D-), U7.42 (USB_DM_DN2)
unnamed: J5.3 (D+), U7.41 (USB_DP_DN2)
unnamed: JP2.1 (A), TP23.1, U9.19 (D+/PS2CLK)
unnamed: JP3.2 (B), TP24.1, U9.20 (D-/BS2DAT)
unnamed: R15.1, U7.32 (USB_R1)
unnamed: R16.2, R17.1, U7.16 (USB_VBUS)
unnamed: R18.1, U9.45 (nLEDFN)
unnamed: R20.1, U9.40 (nLEDCAPS)
unnamed: TP13.1, U7.18 (GRSTz)
unnamed: TP14.1, U7.56 (USB_DP_DN4)
unnamed: TP15.1, U7.57 (USB_DM_DN4)
unnamed: TP16.1, U7.8 (FULLPWRMGMTz/SMBA1)
unnamed: TP17.1, U7.9 (PWRCTL_POL)
unnamed: TP18.1, U7.10 (GANGED/SMBA2/HS_UP)
unnamed: TP19.1, U7.13 (AUTOENz/HS_SUSPEND)
unnamed: TP20.1, U7.6 (SCL/SMBCLK)
unnamed: TP21.1, U7.5 (SDA/SMBDAT)
unnamed: TP22.1, U7.7 (SMBUSz)
USB_HOST_N: U7.22 (USB_DM_UP); also elsewhere on the board
USB_HOST_P: U7.21 (USB_DP_UP); also elsewhere on the board
col0: U9.17 (COL00/PRGC); also elsewhere on the board
col1: U9.22 (COL01/PRGD); also elsewhere on the board
col2: U9.27 (COL02); also elsewhere on the board
col3: U9.28 (COL03); also elsewhere on the board
col4: U9.29 (COL04); also elsewhere on the board
col5: U9.30 (COL05); also elsewhere on the board
col6: U9.31 (COL06); also elsewhere on the board
col7: U9.32 (COL07); also elsewhere on the board
col8: U9.33 (COL08); also elsewhere on the board
col9: U9.34 (COL09); also elsewhere on the board
row0: U9.11 (ROW0); also elsewhere on the board
row1: U9.10 (ROW1); also elsewhere on the board
row2: U9.9 (ROW2); also elsewhere on the board
row3: U9.8 (ROW3); also elsewhere on the board
row4: U9.7 (ROW4); also elsewhere on the board
row5: U9.6 (ROW5); also elsewhere on the board
row6: U9.5 (ROW6); also elsewhere on the board
row7: U9.4 (ROW7); also elsewhere on the board

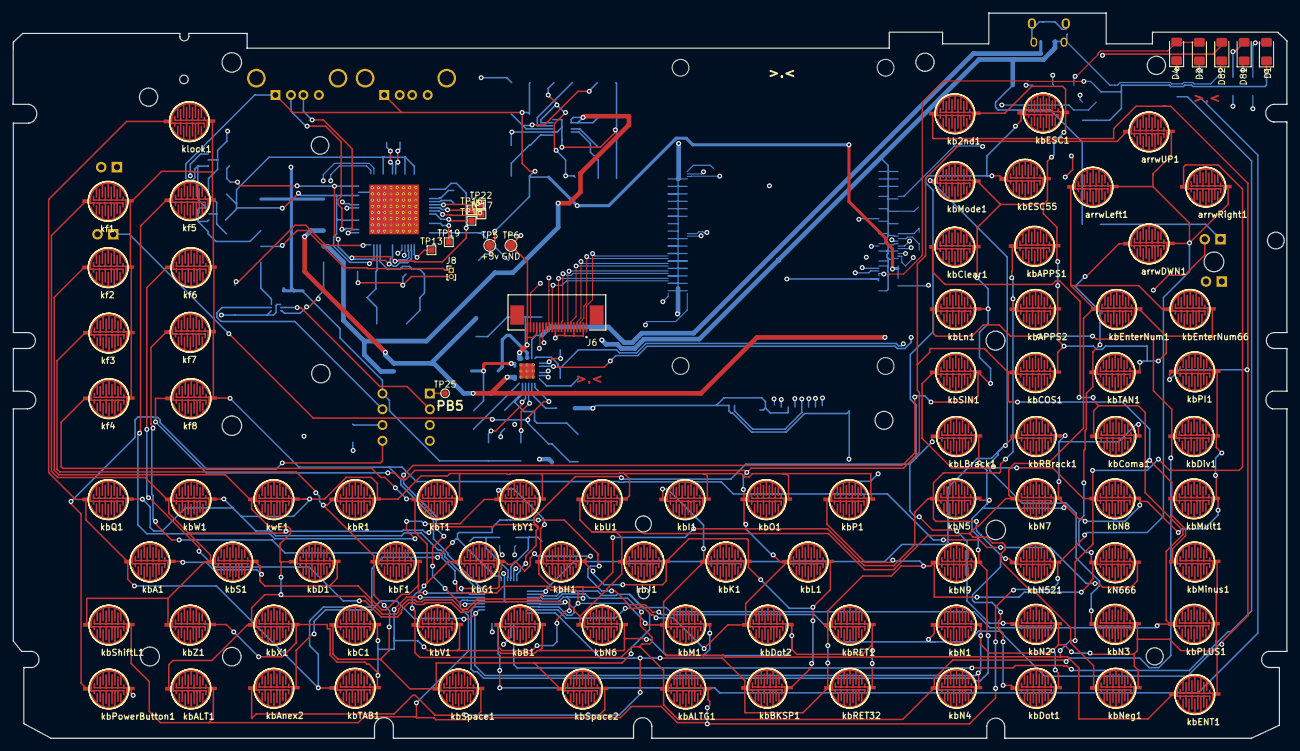
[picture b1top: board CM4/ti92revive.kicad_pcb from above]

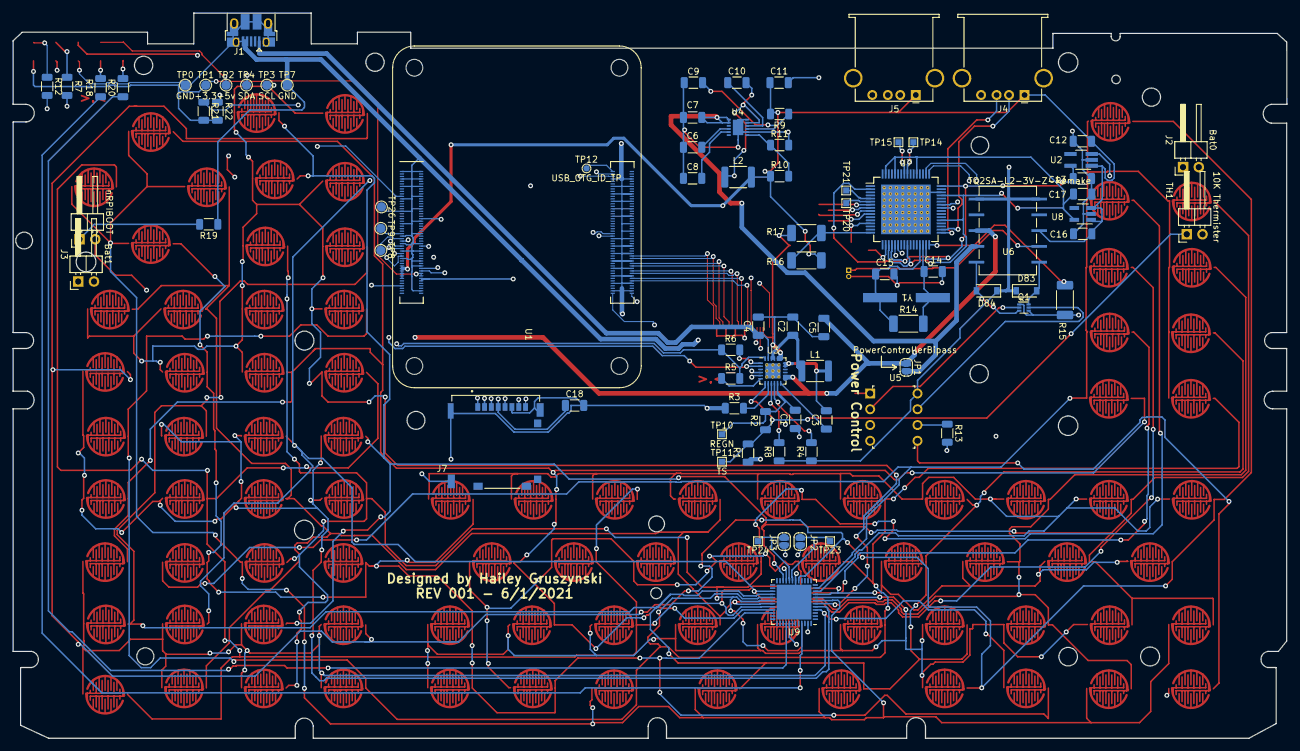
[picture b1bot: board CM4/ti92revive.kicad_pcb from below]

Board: 4 copper layers, 205.0 x 116.7 mm, 185 parts (84 on the bottom side), 112 nets.

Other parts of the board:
C18: 10 uF; C_1206_3216Metric
J7: Micro_SD_Card; MOLEX_503182-1852

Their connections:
+3.3: C18.1, J7.4 (VDD); also elsewhere on the board
Earth_Clean: C18.2, J7.6 (VSS), J7.9 (SHIELD); also elsewhere on the board
SD_CLK: J7.5 (CLK); also elsewhere on the board
SD_CMD: J7.3 (CMD); also elsewhere on the board
SD_DAT0: J7.7 (DAT0); also elsewhere on the board
SD_DAT1: J7.8 (DAT1); also elsewhere on the board
SD_DAT2: J7.1 (DAT2); also elsewhere on the board
SD_DAT3: J7.2 (DAT3/CD); also elsewhere on the board

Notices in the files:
parts and their libraries:
Copyright 2016 Accelerated Designs. All rights reserved.
